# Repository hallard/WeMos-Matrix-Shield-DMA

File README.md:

# ESP32 D1 Mini D1 RGB Matrix Shield 

This shield is the following of this [project](https://github.com/hallard/WeMos-Matrix-Shield) but I created a new repo since the board is different, wiring also and even the library used to drive Matrix.

This board is used to simplify ESP32 connectivity with a nice matric RGB led. This idea came from excellent project called [Morphing Digital Clock][3] done by [HariFun][1] Instructable. But with this library and current code I got some issues with mutitasking, and using same time the awesome Async libraries ([Web Server](https://github.com/me-no-dev/ESPAsyncWebServer) and [MQTT](https://github.com/marvinroger/async-mqtt-client)) getting very ofther in reboot and board reset. I don't blame anyone, the library used was just to drive matrix, it's always complicated mixing some libraries sometimes especially ones with hardware intensive related suff, IRQ's and TCP.

This was until [@mrfaptastic](https://github.com/mrfaptastic/ESP32-HUB75-MatrixPanel-I2S-DMA) released the DMA version wich is far less CPU intensive. I tested this one with Async Web Server, Async MQTT and OTA without any issue. You can participate to the @vortigont started discussion [here](https://github.com/mrfaptastic/ESP32-HUB75-MatrixPanel-I2S-DMA/discussions/96) Thanks to github for this new feature.

See it in action, nice isn't it?

This breakout has just few minimal features.

**New in Version V1.9**

- Touchpad 9 (T9) used and wired to GPIO32
- Exposed (top right corner) GPIO0 instead of GPIO32
- Reversed I2C connector order, because all I2C wiring have components on top except Luminosity TSL2561 BH1750, now fixed
- I2C connector order have drilled holes to match sensor plug, no need to solder to fix or swap sensor type. Just press it to fit into holes
- Added another pin close to I2C connector connected to GPIO34 (for using sensor IRQ pin for example)
- Major re-routing to fix issues

**New in Version V1.8a**

- **this PCB version does not work, please don't use it**
- Added C1, C2, C3 footprints. It's to add capacitor to poor 3.3V VOut of esp32 on board regulator. This one is not output filtered enough resulting sometimes with brownout reset loop. Now you can plug radial or 1 (or 2) SMD 0805 in parallel

**New in DMA Version V1.8**

- **this PCB version does not work, please don't use it**
- Removed ESP8266 compatibility, since DMA need more GPIO it's now exclusive to ESP32 boards with WeMos Mini D1 wiring called ESP32 Mini Kit or ESP32 Wemos, or ESP32 MH-ET Live such as this [banggood model](https://www.banggood.com/Wemos-D1-Mini-ESP32-ESP-32-WiFiBluetooth-Internet-Of-Things-Development-Board-Based-ESP8266-p-1205854.html) or this [aliexpress](https://www.aliexpress.com/item/MH-ET-LIVE-D1-mini-ESP32-ESP-32-WiFi-Bluetooth-Internet-of-Things-development-board-based/32815530502.html). But you can find a lot also on ebay, not a problem.
- PCB board has been extented to fit this ESP32 Mini module .
- LDR to dynamically change brightness according to ambiant light
- I2C connectors as header and Groove to plug a bunch of sensors
- Added one touch pad button
- No need to wire back the shield to HUB75 output of the Matrix Panel

Please check wiring and picture before ordering, should looks like something like that:

**V1.9 are fully tested and working**.

**V1.8 and V1.8a boards are not working** I've been too confident, this is the 1st time I need to throw out all boards. Reason is that both ESP32 headers the ones side by side were reversed (on each side).
I mean the 1st was the 2nd and vice versa), So as you can imagine nothing was unable to works, even flashing ESP32.

# Detailed Description

Look at the schematics for more informations.

# Schematic  

# Boards  

&nbsp;

~~You can order PCBs of this board at [PCBs.io)(ttps://www.pcbs.io/)~~

 ~~PCBs.io give me some reward when you order my designed boards from their site. This is pretty good, because I can use these rewards to create and design new boards and order boards for a discounted price, so if you don't care about PCB manufacturer please use PCBs.io.~~

Looks like PCBs.io is gone, I do not have any rewards from PCBs.io since August 2020 and my free order placed after are still not received, so my guess they are not on business anymore and my $1000 rewards are not usable anymore, too bad.

So you can order the board on [oshpark](https://oshpark.com) or submit gerbers.zip file to any PCB manufacturer of your choice.

- [V1.9](https://oshpark.com/shared_projects/gCeBFgxd)

It's a pitty after several discuss with OSHPark that I can't have any rewards for each people ordering my boards, this would allow me to order free PCB for shared projects and create new ones. For information my shared boards generated a total of **$285 162.00** orders at PCBs.io in 4 years, not bad at all :-)

Hoping one day OSHparks will thanks me giving them this market. 

# Firmware

I suggest you to look at the awesome [examples](https://github.com/mrfaptastic/ESP32-HUB75-MatrixPanel-I2S-DMA/tree/master/examplesk) located in the [library](https://github.com/mrfaptastic/ESP32-HUB75-MatrixPanel-I2S-DMA) driving the Matrix Panel.
 
# Assembled boards

&nbsp;

# BOM

Nothing fancy, just some headers and 2 differents power conector (choose the one you prefer) :

 - 10K 0805 resistor for LDR
 - Any LDR PhotoCell 5528
 - I2C 4.7K resistor 0805 if needed, default I2C set to 3.3V use JP3 if you prefer 5V
 - For better stability C1 100uF 16V electrolytic, or C2 100uF 0805, or C2+C3 47uF 0805
 - Diode can be any Schottky diode barrier and is not mandatory (if not close JP4 jumper)
 - Ebay search for "DC Power Jack Barrel PCB Mount"
 - 7.62mm barrier terminal block [example](https://ebyelectro.com/terminal-block-product-info.asp?ProductID=333)
 - Ebay search for "2X8 Pin 2.54mm Double Row Female Header" or polulu product #1028, you can also use twice 1x8 pin female or even twice 2x4 pins female, plenty of option for this one

# License

This work is licensed under a [Creative Commons Attribution-NonCommercial-ShareAlike 4.0 International License](https://creativecommons.org/licenses/by-nc-sa/4.0/)    

# Misc

See news and other projects on my [blog][2] 

Thanks to @mrfaptastic, @vortigont, @me-no-dev and all other I may forgot.
 
[1]: https://www.instructables.com/member/HariFun/
[2]: https://hallard.me
[3]: https://www.instructables.com/id/Morphing-Digital-Clock/
[4]: https://PCBs.io/share/

[20]: https://wiki.wemos.cc/products:d1:d1_mini_lite
[21]: https://wiki.wemos.cc/products:d1:d1_mini
[22]: https://wiki.wemos.cc/products:d1:d1_mini_pro

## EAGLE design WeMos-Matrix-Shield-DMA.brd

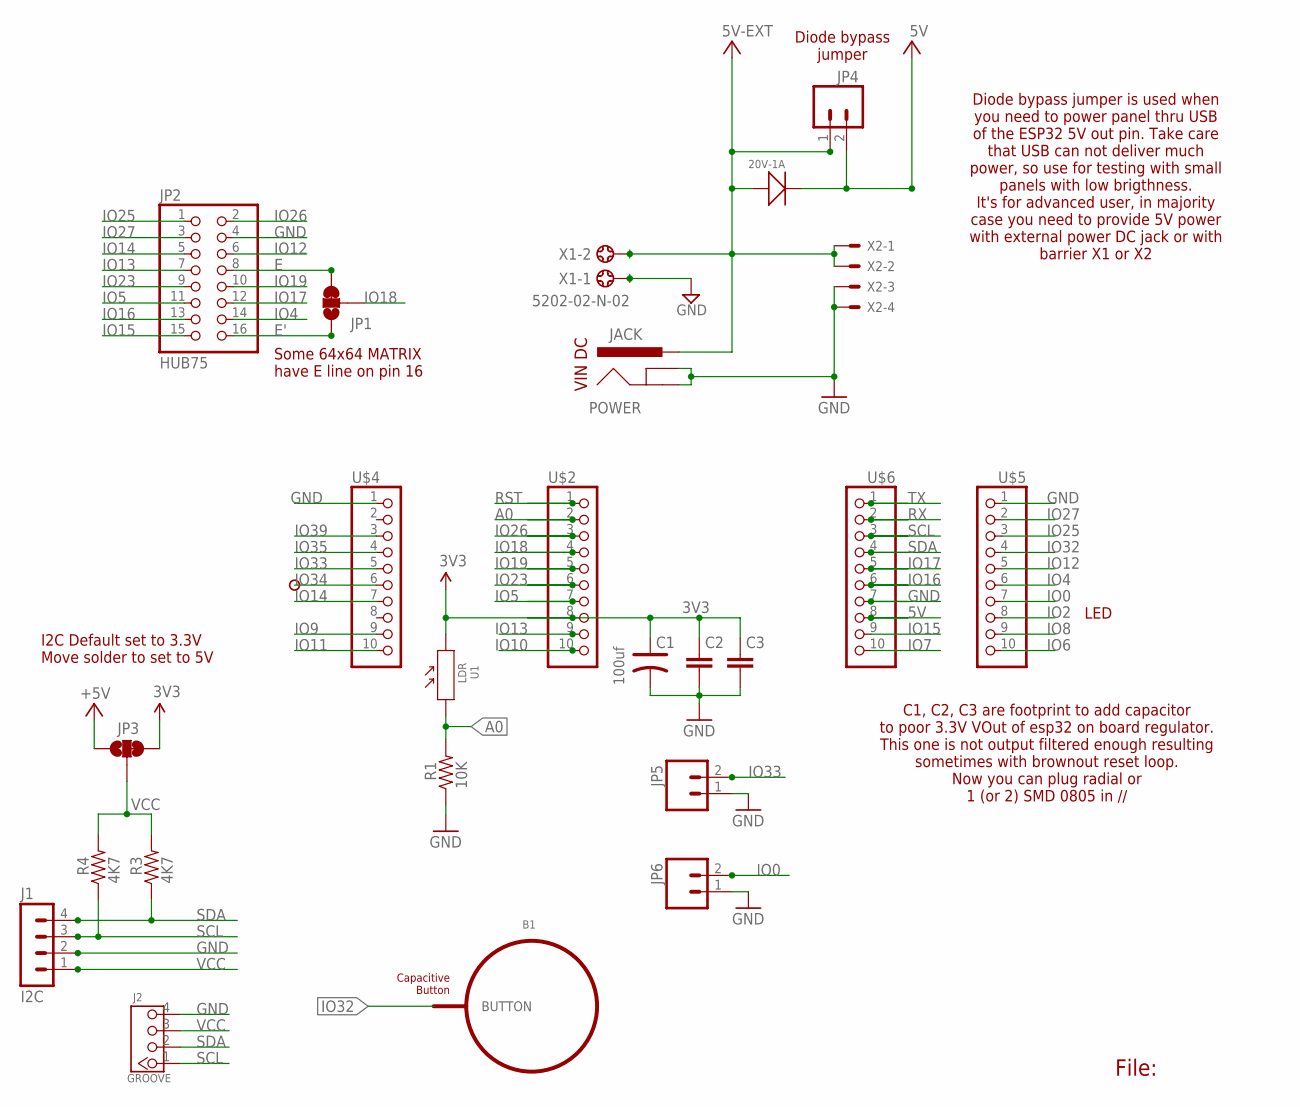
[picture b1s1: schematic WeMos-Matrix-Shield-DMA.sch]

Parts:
B1: BUTTON_PASSIVE6MM; BUTTON_PASSIVE_6MM
C1: 100uf; PC-D5.3MM
C2, C3: CAP0805-CAP-LARGEPADS; 0805-CAP-LARGEPADS
D3: 20V-1A; SOD-123
J1: I2C; 1X04_LOCK_HOLE
J2: GROOVE; 2.0_1X4
JACK: POWER; POWER_JACK_PTH
JP1, JP3: JUMPER-PAD-3-2OF3_NC_BY_TRACE_LARGE; PAD-JUMPER-3-2OF3_NC_BY_TRACE_YES_SILK_LARGE
JP2: HUB75; 2X08
JP4, JP5, JP6: M02; 1X02
P2: PADSMALL; PAD-SMALL
R1: 10K; 0805-RES
R3, R4: 4K7; 0805-RES
U1: LDR; SNR2-3.0
U$2, U$4, U$5, U$6: PINHD-1X10; 1X10-BIG
X1: 5202-02-N-02
X2: KK-156-4

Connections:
3V3: C1.+, C2.1, C3.1, JP3.3, U1.2, U$2.8
5V: D3.-, JP3.1, JP4.2, U$6.8
5V-EXT: D3.+, JACK.PWR, JP4.1, X1.2, X2.1, X2.2
A0: R1.2, U1.1, U$2.2
E: JP1.3, JP2.8
E': JP1.1, JP2.16
GND: C1.-, C2.2, C3.2, J1.2, J2.4, JACK.GND, JACK.GNDBREAK, JP2.4, JP5.1, JP6.1, R1.1, U$4.1, U$5.1, U$6.7, X1.1, X2.3, X2.4
IO0: JP6.2, U$5.7
IO2: U$5.8
IO4: JP2.14, U$5.6
IO5: JP2.11, U$2.7
IO6: U$5.10
IO7: U$6.10
IO8: U$5.9
IO9: U$4.9
IO10: U$2.10
IO11: U$4.10
IO12: JP2.6, U$5.5
IO13: JP2.7, U$2.9
IO14: JP2.5, U$4.7
IO15: JP2.15, U$6.9
IO16: JP2.13, U$6.6
IO17: JP2.12, U$6.5
IO18: JP1.2, U$2.4
IO19: JP2.10, U$2.5
IO23: JP2.9, U$2.6
IO25: JP2.1, U$5.3
IO26: JP2.2, U$2.3
IO27: JP2.3, U$5.2
IO32: B1.BUTTON, U$5.4
IO33: JP5.2, U$4.5
IO34: P2.1, U$4.6
IO35: U$4.4
IO39: U$4.3
RST: U$2.1
RX: U$6.2
SCL: J1.3, J2.1, R4.1, U$6.3
SDA: J1.4, J2.2, R3.1, U$6.4
TX: U$6.1
VCC: J1.1, J2.3, JP3.2, R3.2, R4.2

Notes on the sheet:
File:
VIN DC
I2C Default set to 3.3V Move solder to set to 5V
Some 64x64 MATRIX have E line on pin 16
Diode bypass jumper
Diode bypass jumper is used when you need to power panel thru USB of the ESP32 5V out pin. Take care that USB can not deliver much power, so use for testing with small panels with low brigthness. It's for advanced user, in majority case you need to provide 5V power with external power DC jack or wi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
C1, C2, C3 are footprint to add capacitor to poor 3.3V VOut of esp32 on board regulator. This one is not output filtered enough resulting sometimes with brownout reset loop. Now you can plug radial or 1 (or 2) SMD 0805 in //
LED

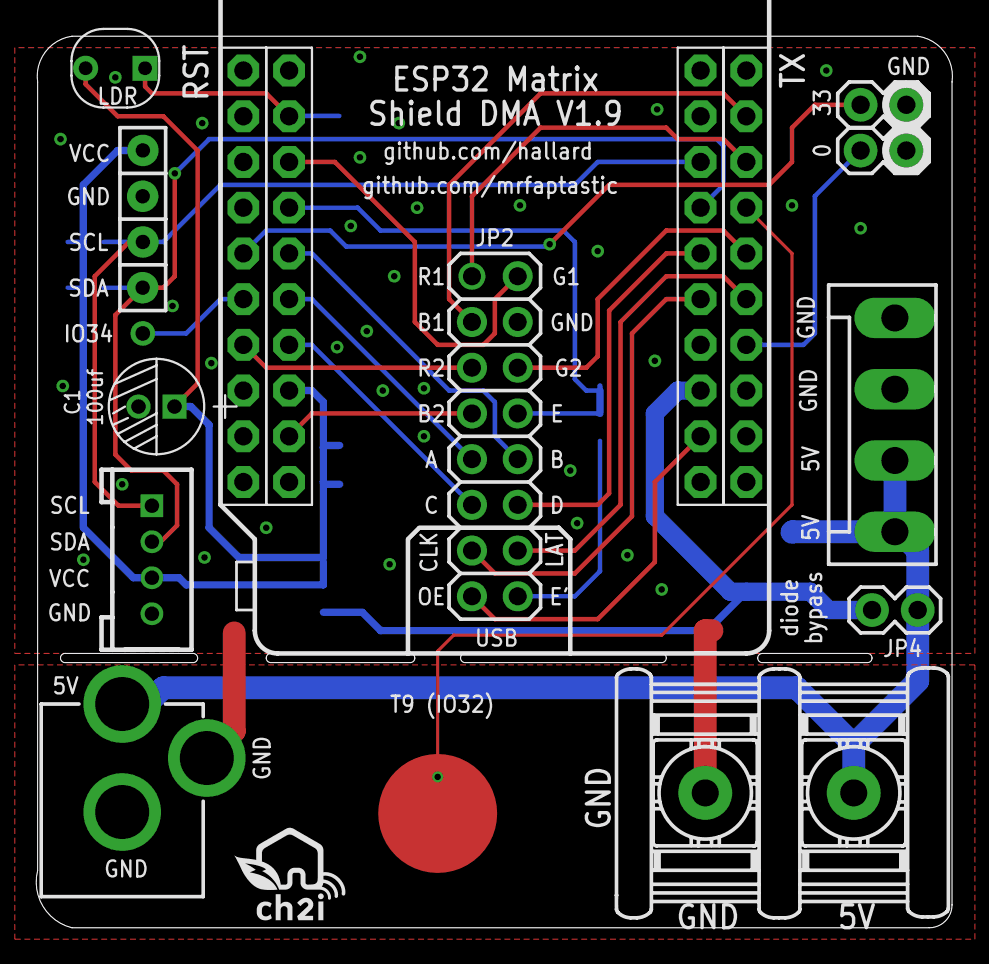
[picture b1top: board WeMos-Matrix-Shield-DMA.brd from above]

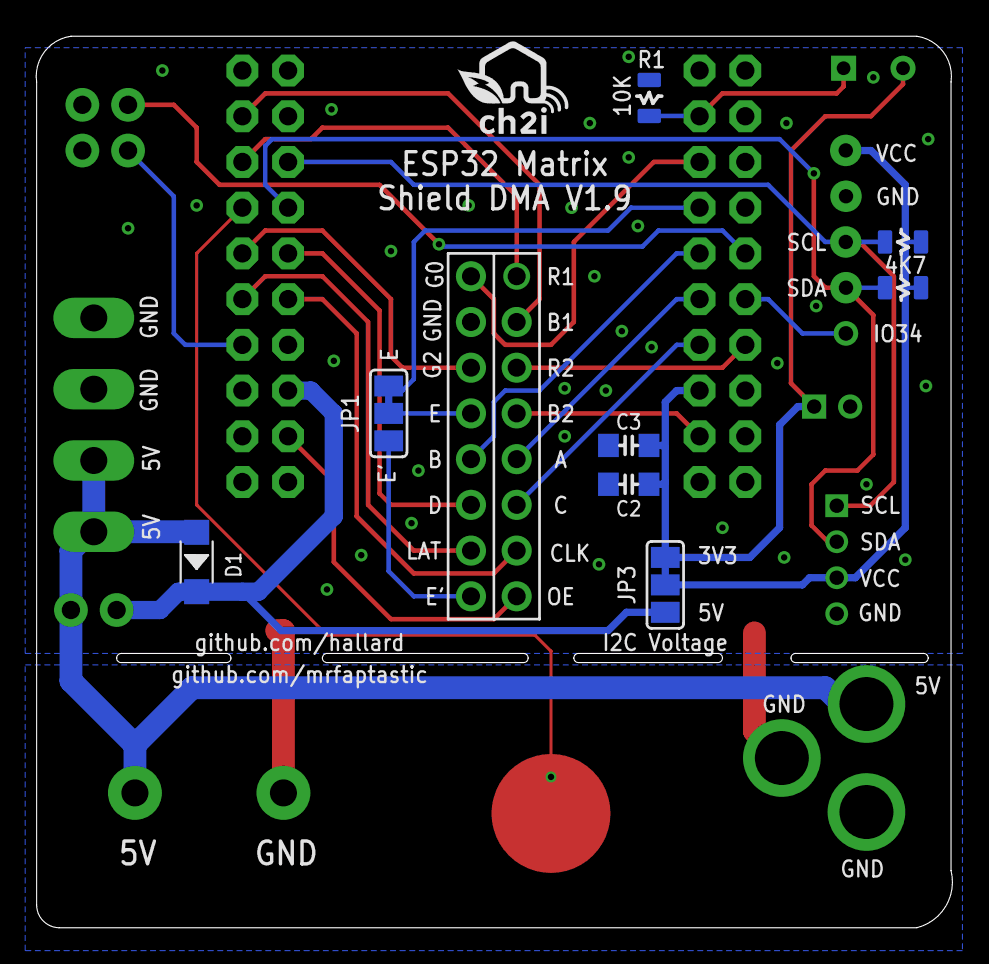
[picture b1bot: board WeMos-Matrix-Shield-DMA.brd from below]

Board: 2 copper layers, 50.9 x 49.5 mm, 27 parts (9 on the bottom side), 28 nets.

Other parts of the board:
U$7, U$8: LOGO_C2I_015

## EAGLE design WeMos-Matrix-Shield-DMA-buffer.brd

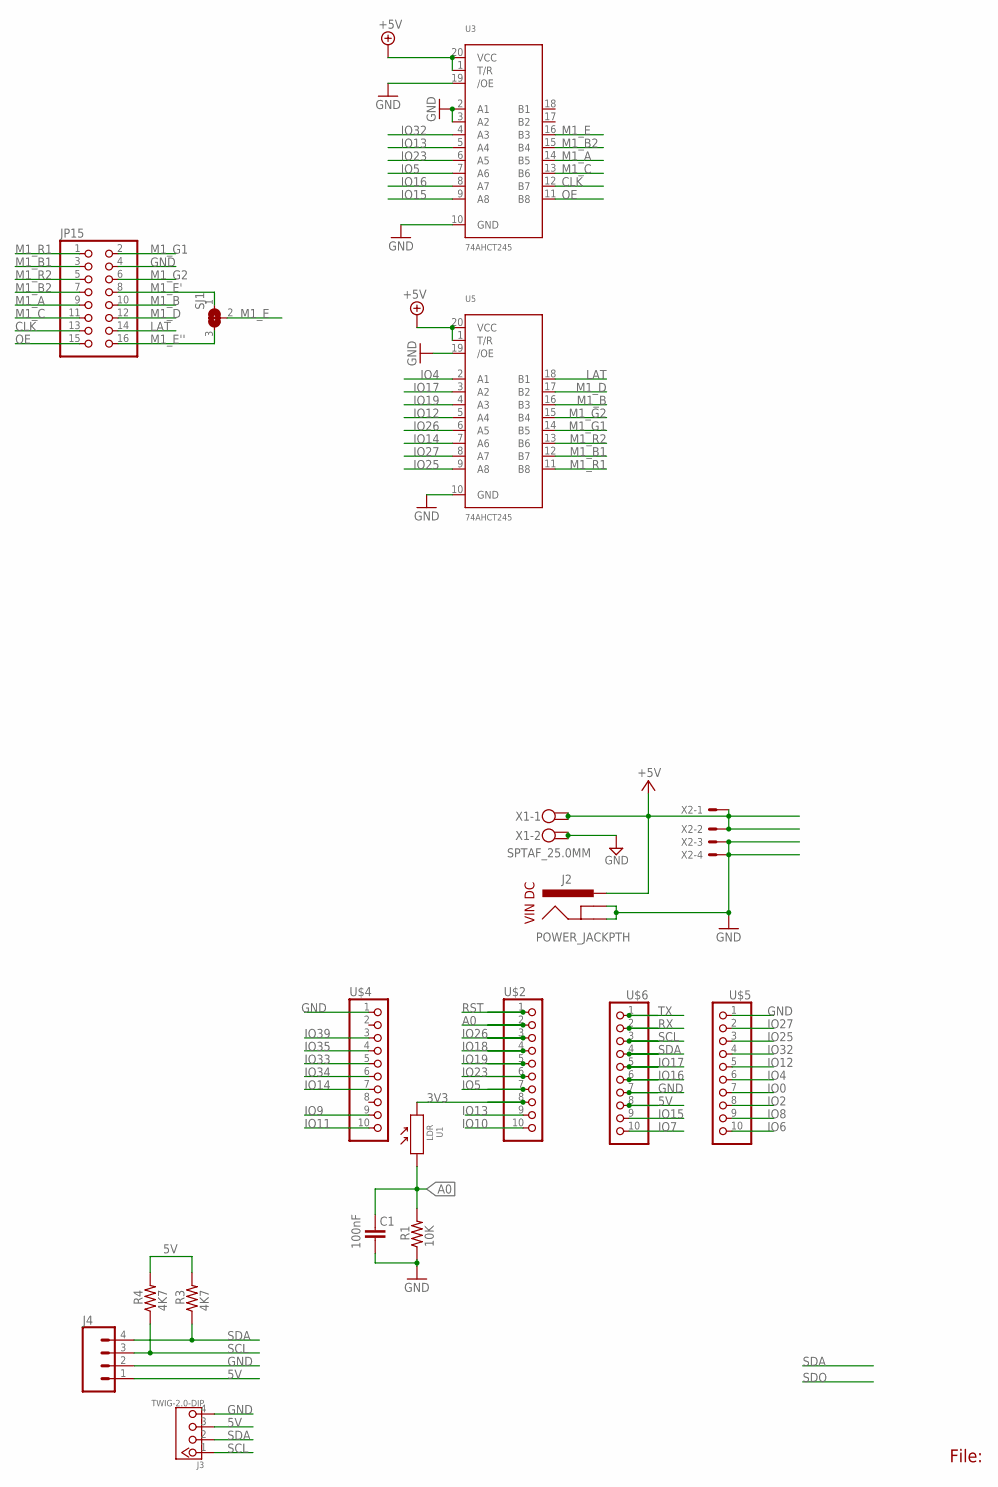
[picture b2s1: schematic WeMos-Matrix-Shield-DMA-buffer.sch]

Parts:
C1: 100nF; 0805-CAP
J2: POWER_JACKPTH; POWER_JACK_PTH
J3: TWIG-2.0-DIP; 2.0_1X4
J4: CONN_04; 1X04
JP15: HEADER-2X8; 2X08
R1: 10K; 0805-RES
R3, R4: 4K7; 0805-RES
SJ1: SOLDERJUMPER_2WAY; SOLDERJUMPER_2WAY_OPEN_NOPASTE
U1: LDR; SNR2-3.0
U3, U5: 74AHCT245; TSSOP20
U$2, U$4, U$5, U$6: PINHD-1X10; 1X10-BIG
X1: SPTAF_25.0MM; SPTAF_2X50
X2: KK-156-4

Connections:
3V3: U1.2, U$2.8
5V: J2.PWR, J3.3, J4.1, R3.2, R4.2, U3.1 (T/R), U3.20 (VCC), U5.1 (T/R), U5.20 (VCC), U$6.8, X1.1, X1.1A (2), X2.1, X2.2
A0: C1.1, R1.2, U1.1, U$2.2
CLK: JP15.13, U3.12 (B7)
GND: C1.2, J2.GND, J2.GNDBREAK, J3.4, J4.2, JP15.4, R1.1, U3.2 (A1), U3.3 (A2), U3.10 (GND), U3.19 (/OE), U5.10 (GND), U5.19 (/OE), U$4.1, U$5.1, U$6.7, X1.2 (1), X1.2A (2), X2.3, X2.4
IO0: U$5.7
IO2: U$5.8
IO4: U5.2 (A1), U$5.6
IO5: U3.7 (A6), U$2.7
IO6: U$5.10
IO7: U$6.10
IO8: U$5.9
IO9: U$4.9
IO11: U$4.10
IO12: U5.5 (A4), U$5.5
IO13: U3.5 (A4)
IO14: U5.7 (A6), U$4.7
IO15: U3.9 (A8), U$6.9
IO16: U3.8 (A7), U$6.6
IO17: U5.3 (A2), U$6.5
IO18: U$2.4
IO19: U5.4 (A3), U$2.5
IO23: U3.6 (A5), U$2.6
IO25: U5.9 (A8), U$5.3
IO26: U5.6 (A5), U$2.3
IO27: U5.8 (A7), U$5.2
IO32: U3.4 (A3), U$5.4
IO33: U$4.5
IO34: U$4.6
IO35: U$4.4
IO39: U$4.3
LAT: JP15.14, U5.18 (B1)
M1_A: JP15.9, U3.14 (B5)
M1_B: JP15.10, U5.16 (B3)
M1_B1: JP15.3, U5.12 (B7)
M1_B2: JP15.7, U3.15 (B4)
M1_C: JP15.11, U3.13 (B6)
M1_D: JP15.12, U5.17 (B2)
M1_E: SJ1.2, U3.16 (B3)
M1_E': JP15.8, SJ1.1
M1_E'': JP15.16, SJ1.3
M1_G1: JP15.2, U5.14 (B5)
M1_G2: JP15.6, U5.15 (B4)
M1_R1: JP15.1, U5.11 (B8)
M1_R2: JP15.5, U5.13 (B6)
OE: JP15.15, U3.11 (B8)
RST: U$2.1
RX: U$6.2
SCL: J3.1, J4.3, R4.1, U$6.3
SDA: J3.2, J4.4, R3.1, U$6.4
TX: U$6.1

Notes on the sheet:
File:
VIN DC

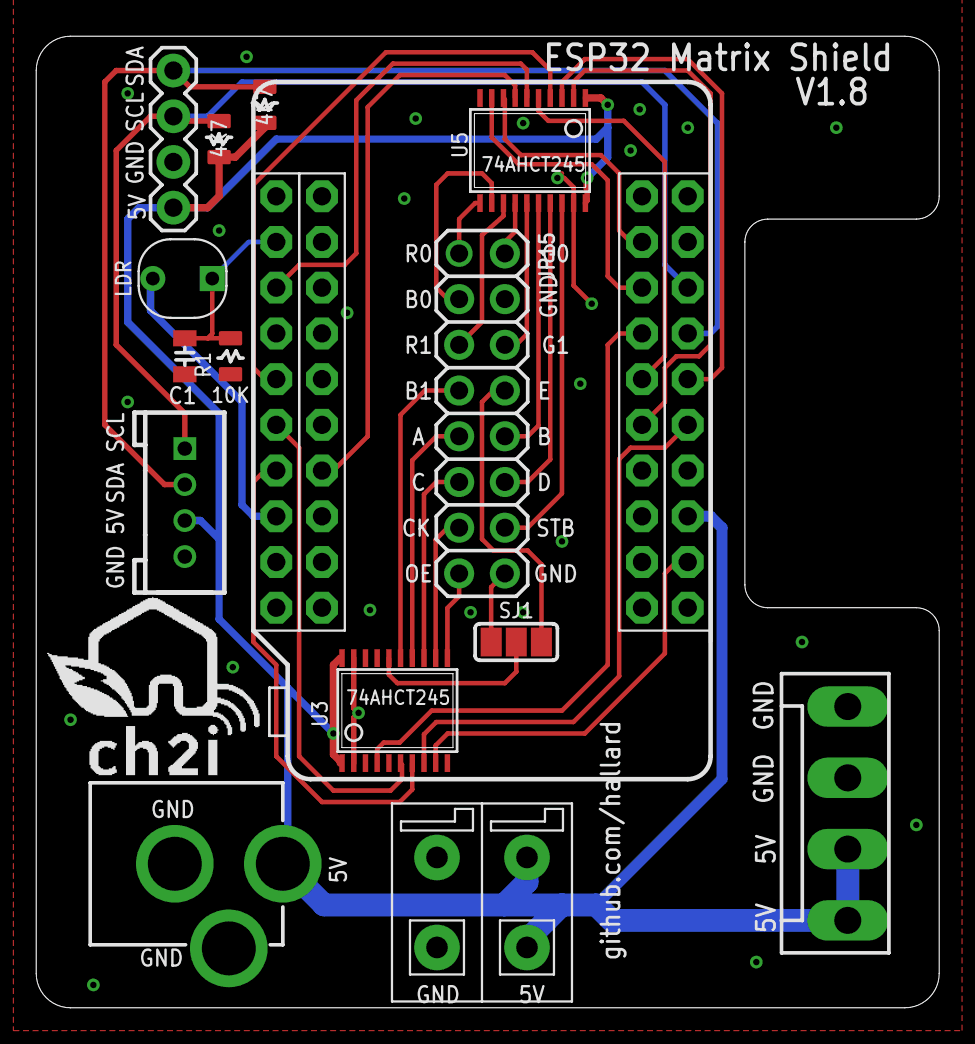
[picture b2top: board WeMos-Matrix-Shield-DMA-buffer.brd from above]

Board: 2 copper layers, 50.2 x 54.0 mm, 20 parts (1 on the bottom side), 35 nets.

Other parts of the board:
U$1, U$3: LOGO_CH2I_110MM

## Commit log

2021-02-27 deleted
2021-02-27 Added oshpark link
2021-02-27 Added gerber files
2021-02-27 cosmetic
2021-02-28 bump to v1.8a
2021-02-28 Changed boards images size
2021-03-16 Updated to V1.9
2021-03-16 Warn on bad v1.8 version
2021-04-22 Marked working + pictures
2026-04-29 Switch to CC BY-NC-SA 4.0 license, add LICENSE file

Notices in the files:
parts and their libraries:
SparkFun-Connectors: Licensing: Creative Commons ShareAlike 4.0 International - https://creativecommons.org/licenses/by-sa/4.0
microbuilder: This work is placed in the public domain, and may be freely used for commercial and non-commercial work with the following conditions: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
